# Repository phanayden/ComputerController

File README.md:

# ComputerController
Custom Computer Controller that uses a custom PCB to control the media functions of the device it is connected to, as well as view the loudness of the room. 

## Key Project Features
* MODE switching button that changes the use of the rotary encoder between VOLUME, MIC GAIN, BRIGHTNESS, and MIC SENSITIVITY
* PLAY, NEXT, BACK, MUTE MIC buttons
* LCD Screen that shows the current volume, mic loudness and gain, mode, if the volume is muted, if the mic is muted, and when each button is pressed
* Each component has a coupling and bulk capacitor
* LED Ring that displays the current volume level in green, and turns red when muted

## Components
* **Microcontroller:** ESP32-S3 N16R8 Development Board
* **Display:** Hosyond 3.5 Inches TFT LCD Touch Screen Shield Display Module 480x320 SPI Serial ILI9488
* **Microphone:** Teyleten Robot MAX9814 Electret Microphone
* **Rotary Encoder:** EC11 Rotary Encoder with Push Button
* **Switches:** GATERON Creamy Keyboard Switches
* **LED Ring:** WS2812B RGB LED Rings 12 Bits

## Hardware Architecture and Visuals
### Circuit Schematic

### Circuit Design

### 3D PCB Layout
TOP

BOTTOM

### Physical PCB

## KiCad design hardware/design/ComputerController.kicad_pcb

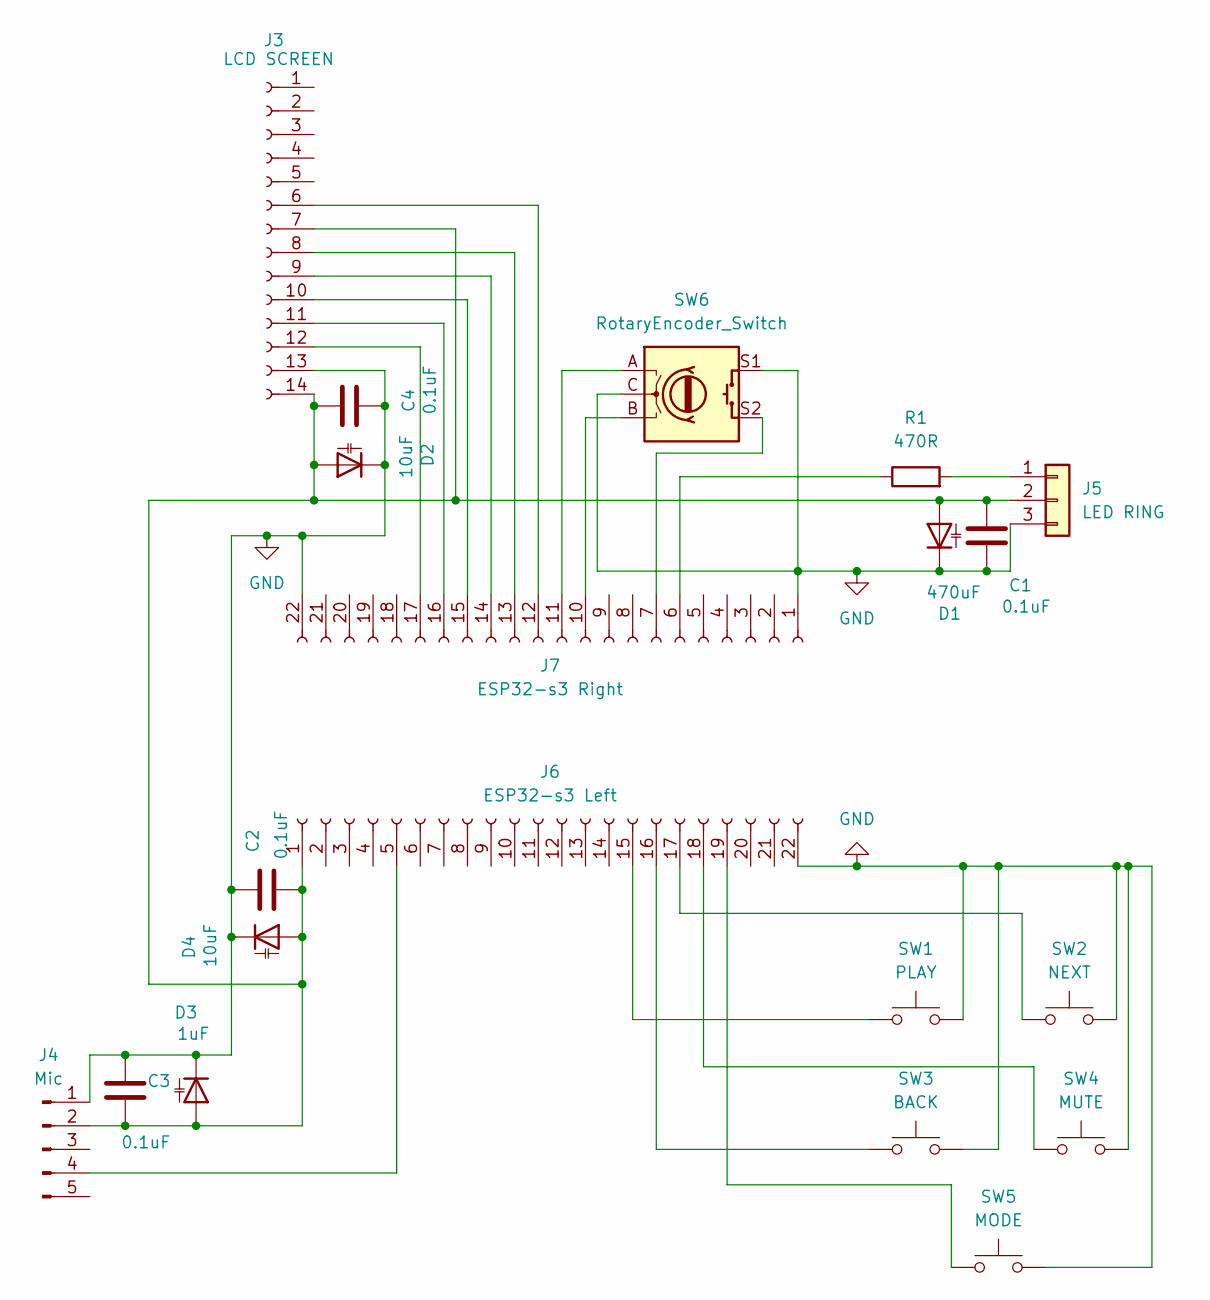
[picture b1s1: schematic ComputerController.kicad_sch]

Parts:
C1, C2, C3, C4: 0.1uF; C_Disc_D5.0mm_W2.5mm_P5.00mm
D1: 470uF; CP_Radial_D6.3mm_P2.50mm
D2, D4: 10uF; CP_Radial_D4.0mm_P2.00mm
D3: 1uF; C_Disc_D7.5mm_W5.0mm_P7.50mm
J3: LCD SCREEN; PinSocket_1x14_P2.54mm_Vertical
J4: Mic; PinHeader_1x05_P2.54mm_Vertical
J5: LED RING; PinHeader_1x03_P2.54mm_Vertical
J6: ESP32-s3 Left; PinSocket_1x22_P2.54mm_Vertical
J7: ESP32-s3 Right; PinSocket_1x22_P2.54mm_Vertical
R1: 470R; R_Axial_DIN0207_L6.3mm_D2.5mm_P7.62mm_Horizontal
SW1: PLAY; SW_Cherry_MX_1.00u_PCB
SW2: NEXT; SW_Cherry_MX_1.00u_PCB
SW3: BACK; SW_Cherry_MX_1.00u_PCB
SW4: MUTE; SW_Cherry_MX_1.00u_PCB
SW5: MODE; SW_Cherry_MX_1.00u_PCB
SW6: RotaryEncoder_Switch; RotaryEncoder_Alps_EC11E-Switch_Vertical_H20mm_MountingHoles

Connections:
GND: C1.2, C2.2, C3.1, C4.2, D1.2 (K), D2.2 (K), D3.2 (K), D4.2 (K), J3.13, J4.1, J5.3, J6.22, J7.1, J7.22, SW1.2, SW2.2, SW3.2, SW4.2, SW5.2, SW6.C, SW6.S1
unnamed: C1.1, C2.1, C3.2, C4.1, D1.1 (A), D2.1 (A), D3.1 (A), D4.1 (A), J3.7, J3.14, J4.2, J5.2, J6.1
unnamed: J3.6, J7.12
unnamed: J3.8, J7.13
unnamed: J3.9, J7.14
unnamed: J3.10, J7.15
unnamed: J3.11, J7.16
unnamed: J3.12, J7.17
unnamed: J4.4, J6.5
unnamed: J5.1, R1.2
unnamed: J6.15, SW1.1
unnamed: J6.16, SW3.1
unnamed: J6.17, SW2.1
unnamed: J6.18, SW4.1
unnamed: J6.19, SW5.1
unnamed: J7.6, R1.1
unnamed: J7.7, SW6.S2
unnamed: J7.10, SW6.B
unnamed: J7.11, SW6.A

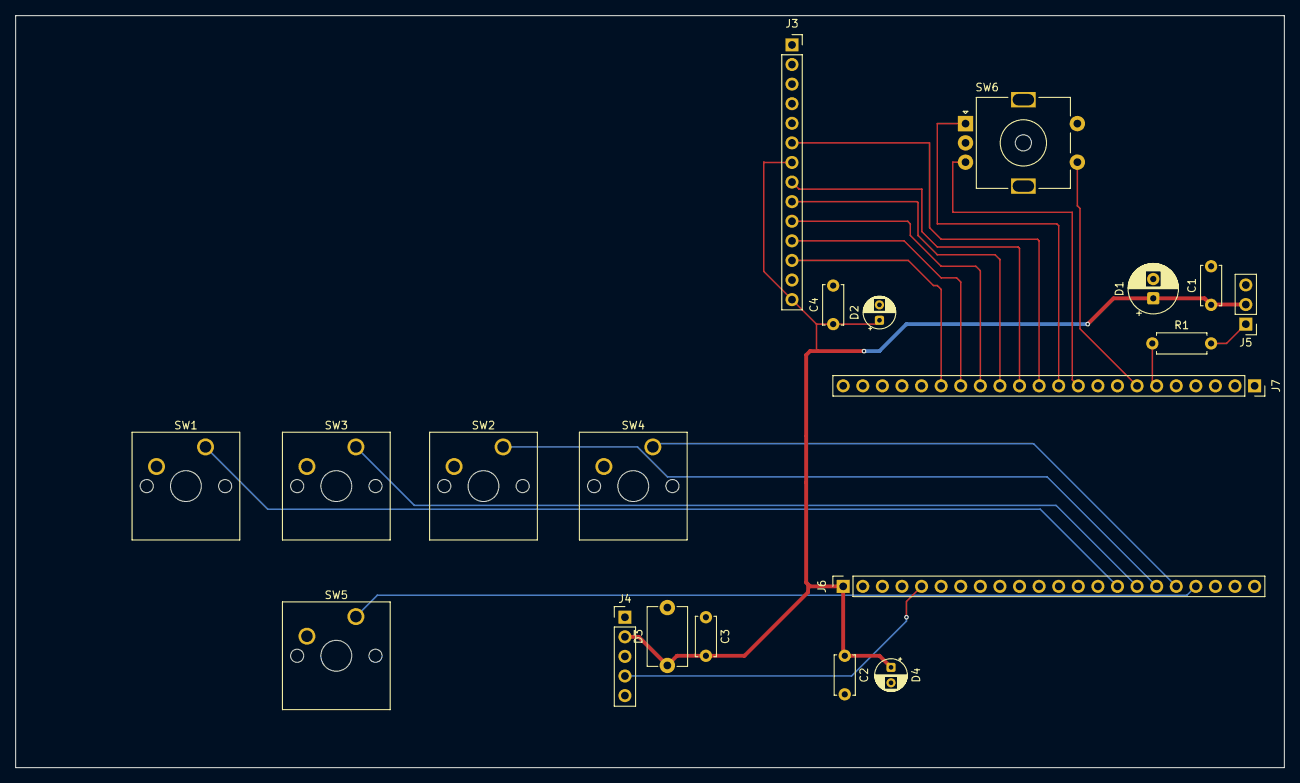
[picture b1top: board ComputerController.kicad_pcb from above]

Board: 2 copper layers, 164.5 x 97.5 mm, 20 parts (0 on the bottom side), 19 nets.
